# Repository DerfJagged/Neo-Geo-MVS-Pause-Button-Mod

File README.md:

# Neo Geo MVS Pause Button Mod v1.1
A simple mod to add pause button functionality to a Neo Geo MVS board.

Created by Derf of [ConsoleMods.org](https://www.consolemods.org/wiki/Main_Page).

Massive thanks to [12voltman](https://github.com/12voltman?tab=repositories) as it wouldn't have been possible without his help!

# Concept and Demo

The Neo Geo MVS does not normally support pausing of games through regular controls. However, (all?) games support a special pause mode when DIP switch #8 is flipped to the ON position during gameplay. This is a graceful pause, as background animations and sound generally continue playing. This mod simply allows you to use a dedicated button on your controller or control panel to electrically toggle this DIP switch. In short, this is a momentary-to-toggle switch board.

Note that this has only been test fit to sit flush on a MV-1AX motherboard. If you install this mod on a different motherboard, please let us know if it sits flush and we can note that here.

Click the image below to see a demo of the mod in action.

# Manufacturing

* Feel free to remove all silkscreen except "ConsoleMods.org".
* 1.0mm thickness recommended.

# Parts

([Shopping cart containing the items below](https://www.digikey.com/en/mylists/list/QAYD25AZV5))

* One AIP74LVC2G14GC363 or equivalent SOT-363 dual inverter Schmitt trigger (INV).
* One SN74LVC1G175DCKR or equivalent SOT-363 flip flop (FLP).
* One MCP130T-315I/TT or equivalent SOT-23-3 chip for Power on Reset (POR).
* One 1kΩ resistor, preferably 0603 size (R1).
* One 10kΩ resistor, preferably 0603 size (R2).
* One 150Ω resistor, preferably 0603 size (R3).
* Two 100nF (0.1µF) capacitors, preferably 0603 size (C1 and C2).

# Installation

1. Assemble pause button PCB. Positions are marked on the board as described in the parts list.
2. Place PCB onto motherboard and align with DIP switch #8 and solder into place. <br> 
3. Solder a wire from a 5V source (such as the "C" pad marked in the picture below or any pad connected to it) to the 5V pad on the PCB.
4. Solder a wire from your desired button to act as the pause button to the SEL pad on the PCB. The suggested button is the Player 1 Select button marked in an image below. Multiple buttons can be wired to the SEL pad at once.
    - For a MV-1C: <br> 
    - For a MV-1AX: <br> 
7. Press the pause button during gameplay to pause the game!
    - If UniBIOS is installed, you will need to first press Select to pause the system, then hold Start and press Select to access the UniBIOS menu.

# Schematic

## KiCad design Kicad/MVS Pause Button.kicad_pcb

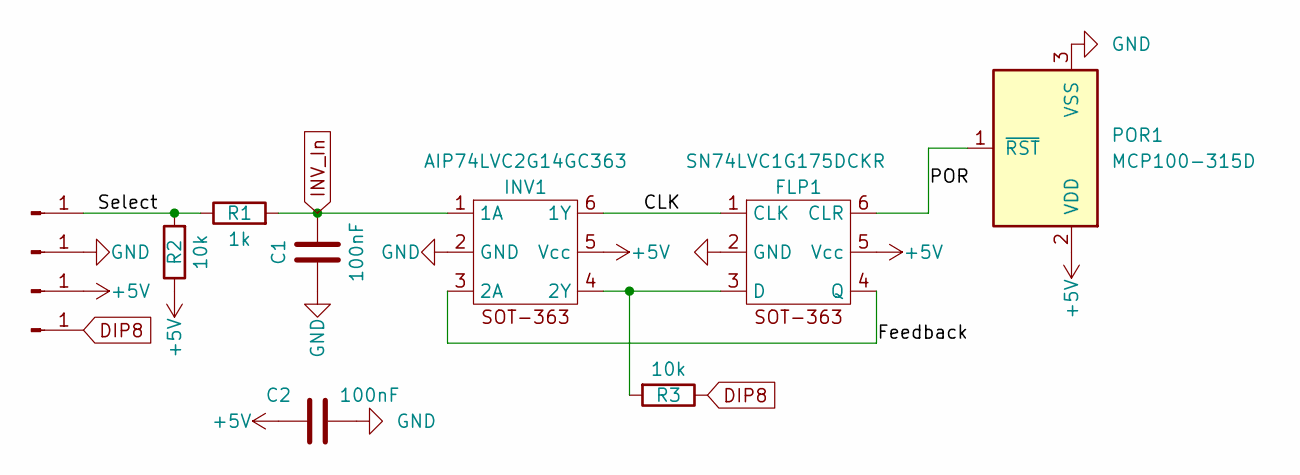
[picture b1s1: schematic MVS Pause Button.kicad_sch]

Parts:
C1, C2: 100nF; C_0603_1608Metric_Pad1.08x0.95mm_HandSolder
FLP1: SN74LVC1G175DCKR; SOT-363_SC-70-6_Handsoldering
INV1: AIP74LVC2G14GC363; SOT-363_SC-70-6_Handsoldering
J1, J3: Conn_01x01_Male; TestPoint_Pad_2.0x2.0mm
J2, J4: Conn_01x01_Male; TestPoint_THTPad_D2.5mm_Drill1.2mm
POR1: MCP100-315D; SOT-23_Handsoldering
R1: 1k; R_0603_1608Metric_Pad0.98x0.95mm_HandSolder
R2, R3: 10k; R_0603_1608Metric_Pad0.98x0.95mm_HandSolder

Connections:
+5V: C2.1, FLP1.5 (Vcc), INV1.5 (Vcc), J3.1, POR1.2 (VDD), R2.1
/CLK: FLP1.1 (CLK), INV1.6 (1Y)
/Feedback: FLP1.4 (Q), INV1.3 (2A)
/POR: FLP1.6 (CLR), POR1.1 (~RST)
/Select: J1.1, R1.1, R2.2
DIP8: J4.1, R3.1
GND: C1.1, C2.2, FLP1.2 (GND), INV1.2 (GND), J2.1, POR1.3 (VSS)
INV_In: C1.2, INV1.1 (1A), R1.2
unnamed: FLP1.3 (D), INV1.4 (2Y), R3.2

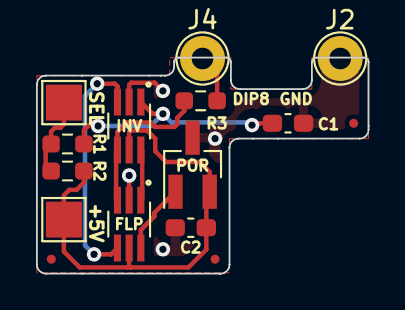
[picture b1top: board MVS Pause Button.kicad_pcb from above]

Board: 2 copper layers, 18.4 x 12.0 mm, 12 parts (0 on the bottom side), 9 nets.

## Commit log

2023-08-02 v1.0
2023-08-10 v1.1
    v1.1
2023-08-16 Update README.md
    Thanks Harcroft!
2023-08-20 Update label
2024-02-21 Added MV-1C pictures and UniBIOS info
